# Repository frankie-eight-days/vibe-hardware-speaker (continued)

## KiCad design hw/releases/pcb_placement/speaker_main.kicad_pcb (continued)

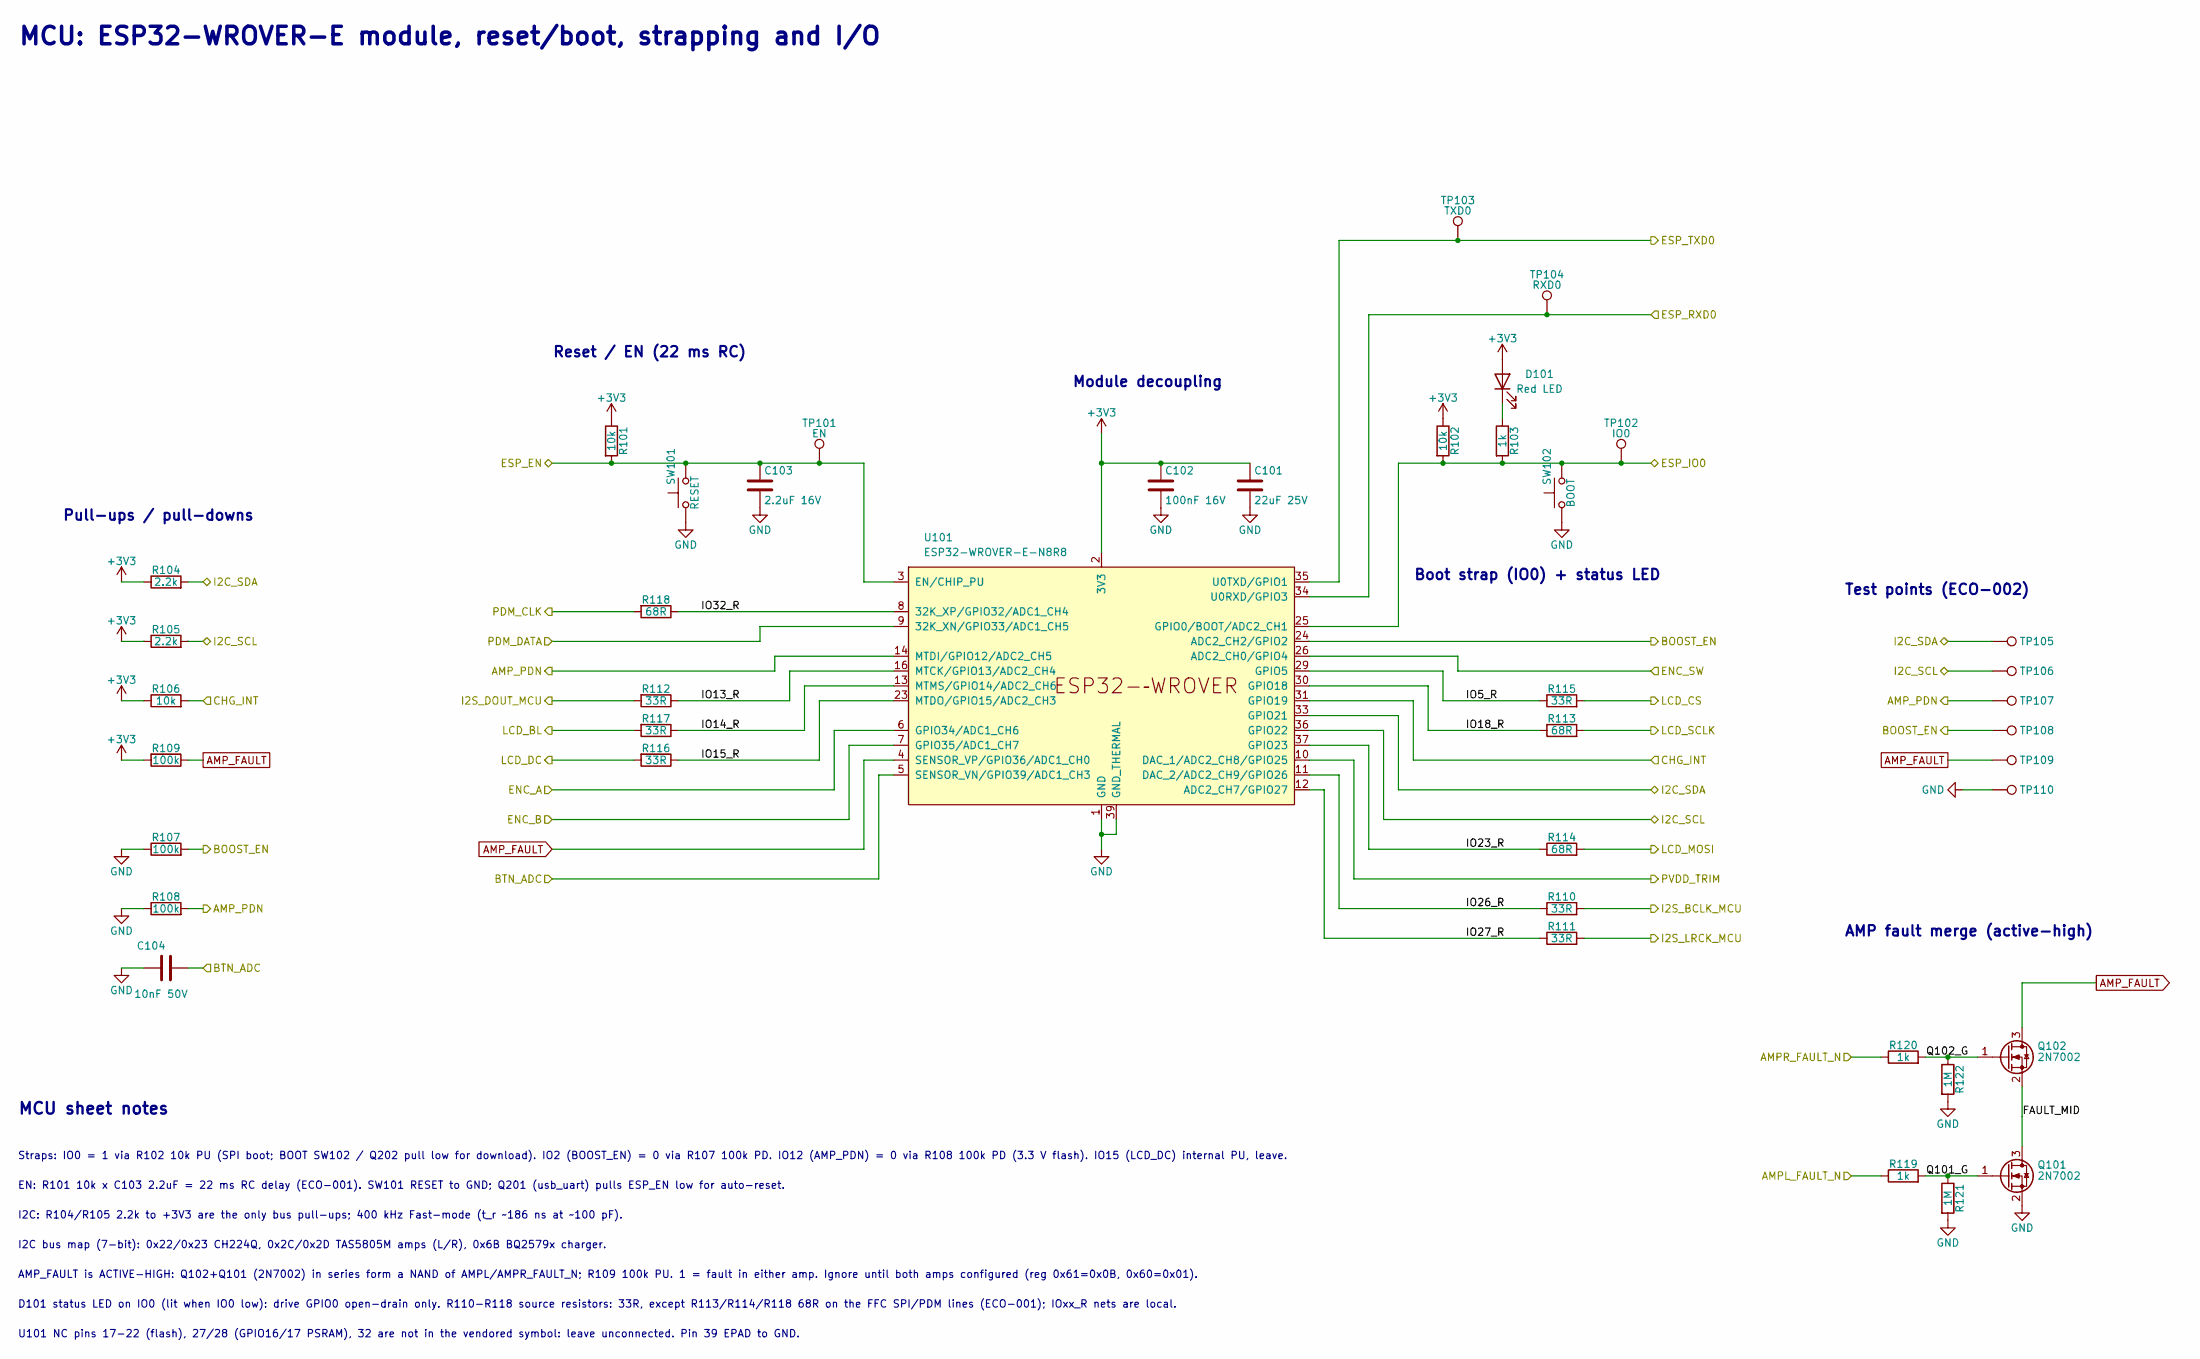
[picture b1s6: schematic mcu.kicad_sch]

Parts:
C101: 22uF 25V; C_0805_2012Metric; LCSC C45783
C102: 100nF 16V; C_0402_1005Metric; LCSC C1525
C103: 2.2uF 16V; C_0402_1005Metric; LCSC C170151
C104: 10nF 50V; C_0402_1005Metric; LCSC C15195
D101: Red LED; LED_0603_1608Metric; LCSC C2286
Q101, Q102: 2N7002; SOT-23; LCSC C8545
R101, R102, R106: 10k; R_0402_1005Metric; LCSC C25744
R103, R119, R120: 1k; R_0402_1005Metric; LCSC C11702
R104, R105: 2.2k; R_0402_1005Metric; LCSC C25879
R107, R108, R109: 100k; R_0402_1005Metric; LCSC C25741
R110, R111, R112, R115, R116, R117: 33R; R_0402_1005Metric; LCSC C25105
R113, R114, R118: 68R; R_0402_1005Metric; LCSC C25131
R121, R122: 1M; R_0402_1005Metric; LCSC C26083
SW101: RESET; SW_Push_1P1T_XKB_TS-1187A; LCSC C318884
SW102: BOOT; SW_Push_1P1T_XKB_TS-1187A; LCSC C318884
TP101: EN; TestPoint_Pad_D1.0mm
TP102: IO0; TestPoint_Pad_D1.0mm
TP103: TXD0; TestPoint_Pad_D1.0mm
TP104: RXD0; TestPoint_Pad_D1.0mm
TP105: I2C_SDA; TestPoint_Pad_D1.0mm
TP106: I2C_SCL; TestPoint_Pad_D1.0mm
TP107: AMP_PDN; TestPoint_Pad_D1.0mm
TP108: BOOST_EN; TestPoint_Pad_D1.0mm
TP109: AMP_FAULT; TestPoint_Pad_D1.0mm
TP110: GND; TestPoint_Pad_D2.0mm
U101: ESP32-WROVER-E-N8R8; ESP32-WROVER-E; LCSC C2973667

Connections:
+3V3: C101.1, C102.1, D101.2 (A), R101.1, R102.1, R104.1, R105.1, R106.1, R109.2, U101.2 (3V3); also elsewhere on the board
/AMPL_FAULT_N: R119.1; also elsewhere on the board
/AMPR_FAULT_N: R120.1; also elsewhere on the board
/AMP_PDN: R108.2, TP107.1 (1_1), U101.14 (MTDI/GPIO12/ADC2_CH5); also elsewhere on the board
/I2C_SCL: R105.2, TP106.1 (1_1), U101.36 (GPIO22); also elsewhere on the board
/I2C_SDA: R104.2, TP105.1 (1_1), U101.33 (GPIO21); also elsewhere on the board
/charger/CHG_INT: R106.2, U101.31 (GPIO19); also elsewhere on the board
/mcu/BOOST_EN: R107.2, TP108.1 (1_1), U101.24 (ADC2_CH2/GPIO2); also elsewhere on the board
/mcu/BTN_ADC: C104.2, U101.5 (SENSOR_VN/GPIO39/ADC1_CH3); also elsewhere on the board
/mcu/ENC_A: U101.6 (GPIO34/ADC1_CH6); also elsewhere on the board
/mcu/ENC_B: U101.7 (GPIO35/ADC1_CH7); also elsewhere on the board
/mcu/ENC_SW: U101.26 (ADC2_CH0/GPIO4); also elsewhere on the board
/mcu/ESP_EN: C103.1, R101.2, SW101.2, TP101.1 (1_1), U101.3 (EN/CHIP_PU); also elsewhere on the board
/mcu/ESP_IO0: R102.2, R103.2, SW102.2, TP102.1 (1_1), U101.25 (GPIO0/BOOT/ADC2_CH1); also elsewhere on the board
/mcu/ESP_RXD0: TP104.1 (1_1), U101.34 (U0RXD/GPIO3); also elsewhere on the board
/mcu/ESP_TXD0: TP103.1 (1_1), U101.35 (U0TXD/GPIO1); also elsewhere on the board
/mcu/FAULT_MID: Q101.3 (D), Q102.2 (S)
/mcu/I2S_BCLK_MCU: R110.2; also elsewhere on the board
/mcu/I2S_DOUT_MCU: R112.2; also elsewhere on the board
/mcu/I2S_LRCK_MCU: R111.2; also elsewhere on the board
/mcu/IO5_R: R115.1, U101.29 (GPIO5)
/mcu/IO13_R: R112.1, U101.16 (MTCK/GPIO13/ADC2_CH4)
/mcu/IO14_R: R117.1, U101.13 (MTMS/GPIO14/ADC2_CH6)
/mcu/IO15_R: R116.1, U101.23 (MTDO/GPIO15/ADC2_CH3)
/mcu/IO18_R: R113.1, U101.30 (GPIO18)
/mcu/IO23_R: R114.1, U101.37 (GPIO23)
/mcu/IO26_R: R110.1, U101.11 (DAC_2/ADC2_CH9/GPIO26)
/mcu/IO27_R: R111.1, U101.12 (ADC2_CH7/GPIO27)
/mcu/IO32_R: R118.1, U101.8 (32K_XP/GPIO32/ADC1_CH4)
/mcu/LCD_BL: R117.2; also elsewhere on the board
/mcu/LCD_CS: R115.2; also elsewhere on the board
/mcu/LCD_DC: R116.2; also elsewhere on the board
/mcu/LCD_MOSI: R114.2; also elsewhere on the board
/mcu/LCD_SCLK: R113.2; also elsewhere on the board
/mcu/PDM_CLK: R118.2; also elsewhere on the board
/mcu/PDM_DATA: U101.9 (32K_XN/GPIO33/ADC1_CH5); also elsewhere on the board
/mcu/PVDD_TRIM: U101.10 (DAC_1/ADC2_CH8/GPIO25); also elsewhere on the board
/mcu/Q101_G: Q101.1 (G), R119.2, R121.1
/mcu/Q102_G: Q102.1 (G), R120.2, R122.1
AMP_FAULT: Q102.3 (D), R109.1, TP109.1 (1_1), U101.4 (SENSOR_VP/GPIO36/ADC1_CH0)
unnamed: D101.1 (K), R103.1

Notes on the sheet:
MCU sheet notes
Straps: IO0 = 1 via R102 10k PU (SPI boot; BOOT SW102 / Q202 pull low for download). IO2 (BOOST_EN) = 0 via R107 100k PD. IO12 (AMP_PDN) = 0 via R108 100k PD (3.3 V flash). IO15 (LCD_DC) internal PU, leave.
I2C: R104/R105 2.2k to +3V3 are the only bus pull-ups; 400 kHz Fast-mode (t_r ~186 ns at ~100 pF).
I2C bus map (7-bit): 0x22/0x23 CH224Q, 0x2C/0x2D TAS5805M amps (L/R), 0x6B BQ2579x charger.
AMP_FAULT is ACTIVE-HIGH: Q102+Q101 (2N7002) in series form a NAND of AMPL/AMPR_FAULT_N; R109 100k PU. 1 = fault in either amp. Ignore until both amps configured (reg 0x61=0x0B, 0x60=0x01).
U101 NC pins 17-22 (flash), 27/28 (GPIO16/17 PSRAM), 32 are not in the vendored symbol: leave unconnected. Pin 39 EPAD to GND.
MCU: ESP32-WROVER-E module, reset/boot, strapping and I/O
Pull-ups / pull-downs
Boot strap (IO0) + status LED
Module decoupling
AMP fault merge (active-high)
EN: R101 10k x C103 2.2uF = 22 ms RC delay (ECO-001). SW101 RESET to GND; Q201 (usb_uart) pulls ESP_EN low for auto-reset.
D101 status LED on IO0 (lit when IO0 low): drive GPIO0 open-drain only. R110-R118 source resistors: 33R, except R113/R114/R118 68R on the FFC SPI/PDM lines (ECO-001); IOxx_R nets are local.
Reset / EN (22 ms RC)
Test points (ECO-002)

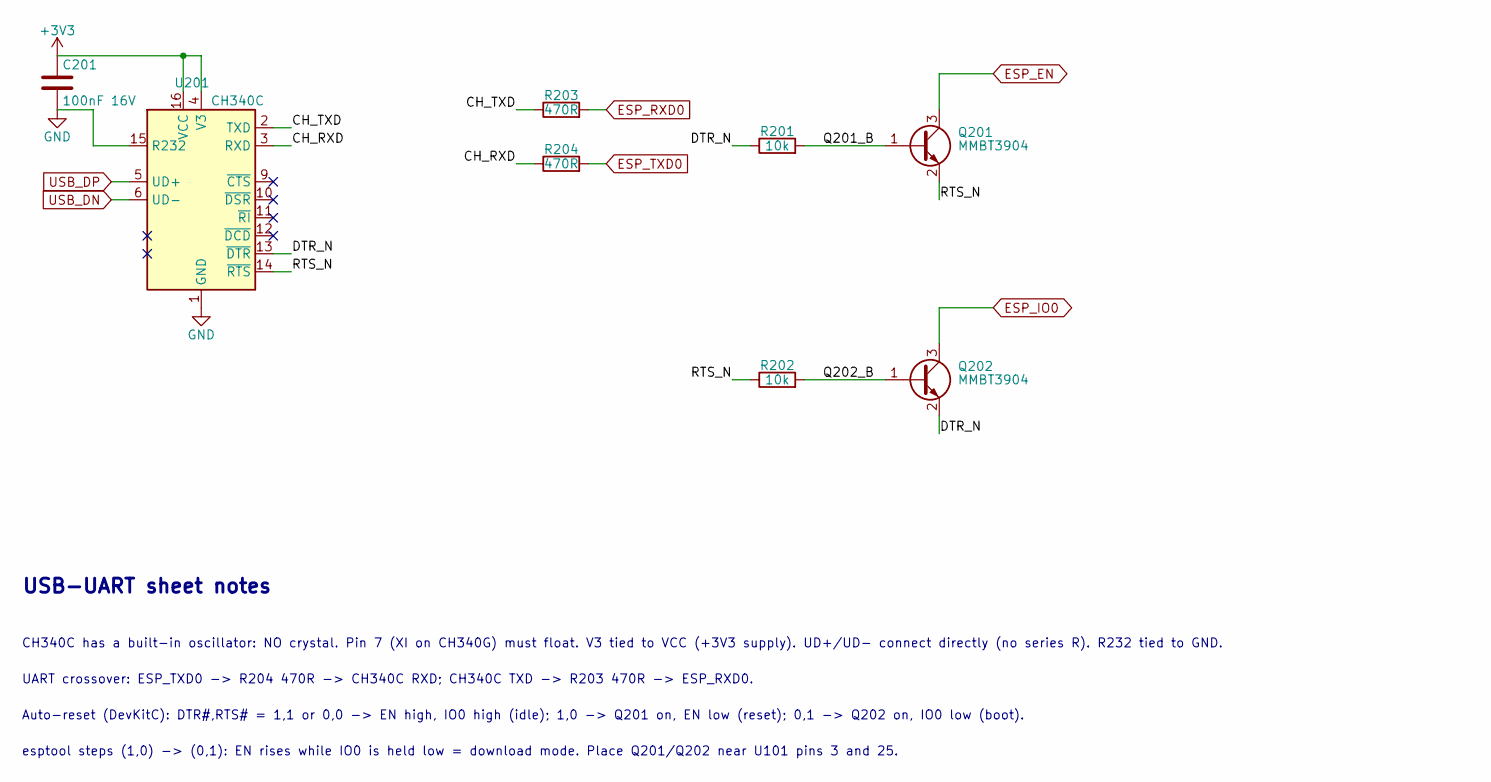
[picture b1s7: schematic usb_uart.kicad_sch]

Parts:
C201: 100nF 16V; C_0402_1005Metric; LCSC C1525
Q201, Q202: MMBT3904; SOT-23; LCSC C20526
R201, R202: 10k; R_0402_1005Metric; LCSC C25744
R203, R204: 470R; R_0402_1005Metric; LCSC C25117
U201: CH340C; SOIC-16_3.9x9.9mm_P1.27mm; LCSC C84681

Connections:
+3V3: C201.1, U201.4 (V3), U201.16 (VCC); also elsewhere on the board
/mcu/ESP_EN: Q201.3 (C); also elsewhere on the board
/mcu/ESP_IO0: Q202.3 (C); also elsewhere on the board
/mcu/ESP_RXD0: R203.2; also elsewhere on the board
/mcu/ESP_TXD0: R204.2; also elsewhere on the board
/usb_power/USB_DN: U201.6 (UD-); also elsewhere on the board
/usb_power/USB_DP: U201.5 (UD+); also elsewhere on the board
/usb_uart/CH_RXD: R204.1, U201.3 (RXD)
/usb_uart/CH_TXD: R203.1, U201.2 (TXD)
/usb_uart/DTR_N: Q202.2 (E), R201.1, U201.13 (~DTR)
/usb_uart/Q201_B: Q201.1 (B), R201.2
/usb_uart/Q202_B: Q202.1 (B), R202.2
/usb_uart/RTS_N: Q201.2 (E), R202.1, U201.14 (~RTS)

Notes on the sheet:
USB-UART sheet notes
CH340C has a built-in oscillator: NO crystal. Pin 7 (XI on CH340G) must float. V3 tied to VCC (+3V3 supply). UD+/UD- connect directly (no series R). R232 tied to GND.
UART crossover: ESP_TXD0 -> R204 470R -> CH340C RXD; CH340C TXD -> R203 470R -> ESP_RXD0.
Auto-reset (DevKitC): DTR#,RTS# = 1,1 or 0,0 -> EN high, IO0 high (idle); 1,0 -> Q201 on, EN low (reset); 0,1 -> Q202 on, IO0 low (boot).
esptool steps (1,0) -> (0,1): EN rises while IO0 is held low = download mode. Place Q201/Q202 near U101 pins 3 and 25.

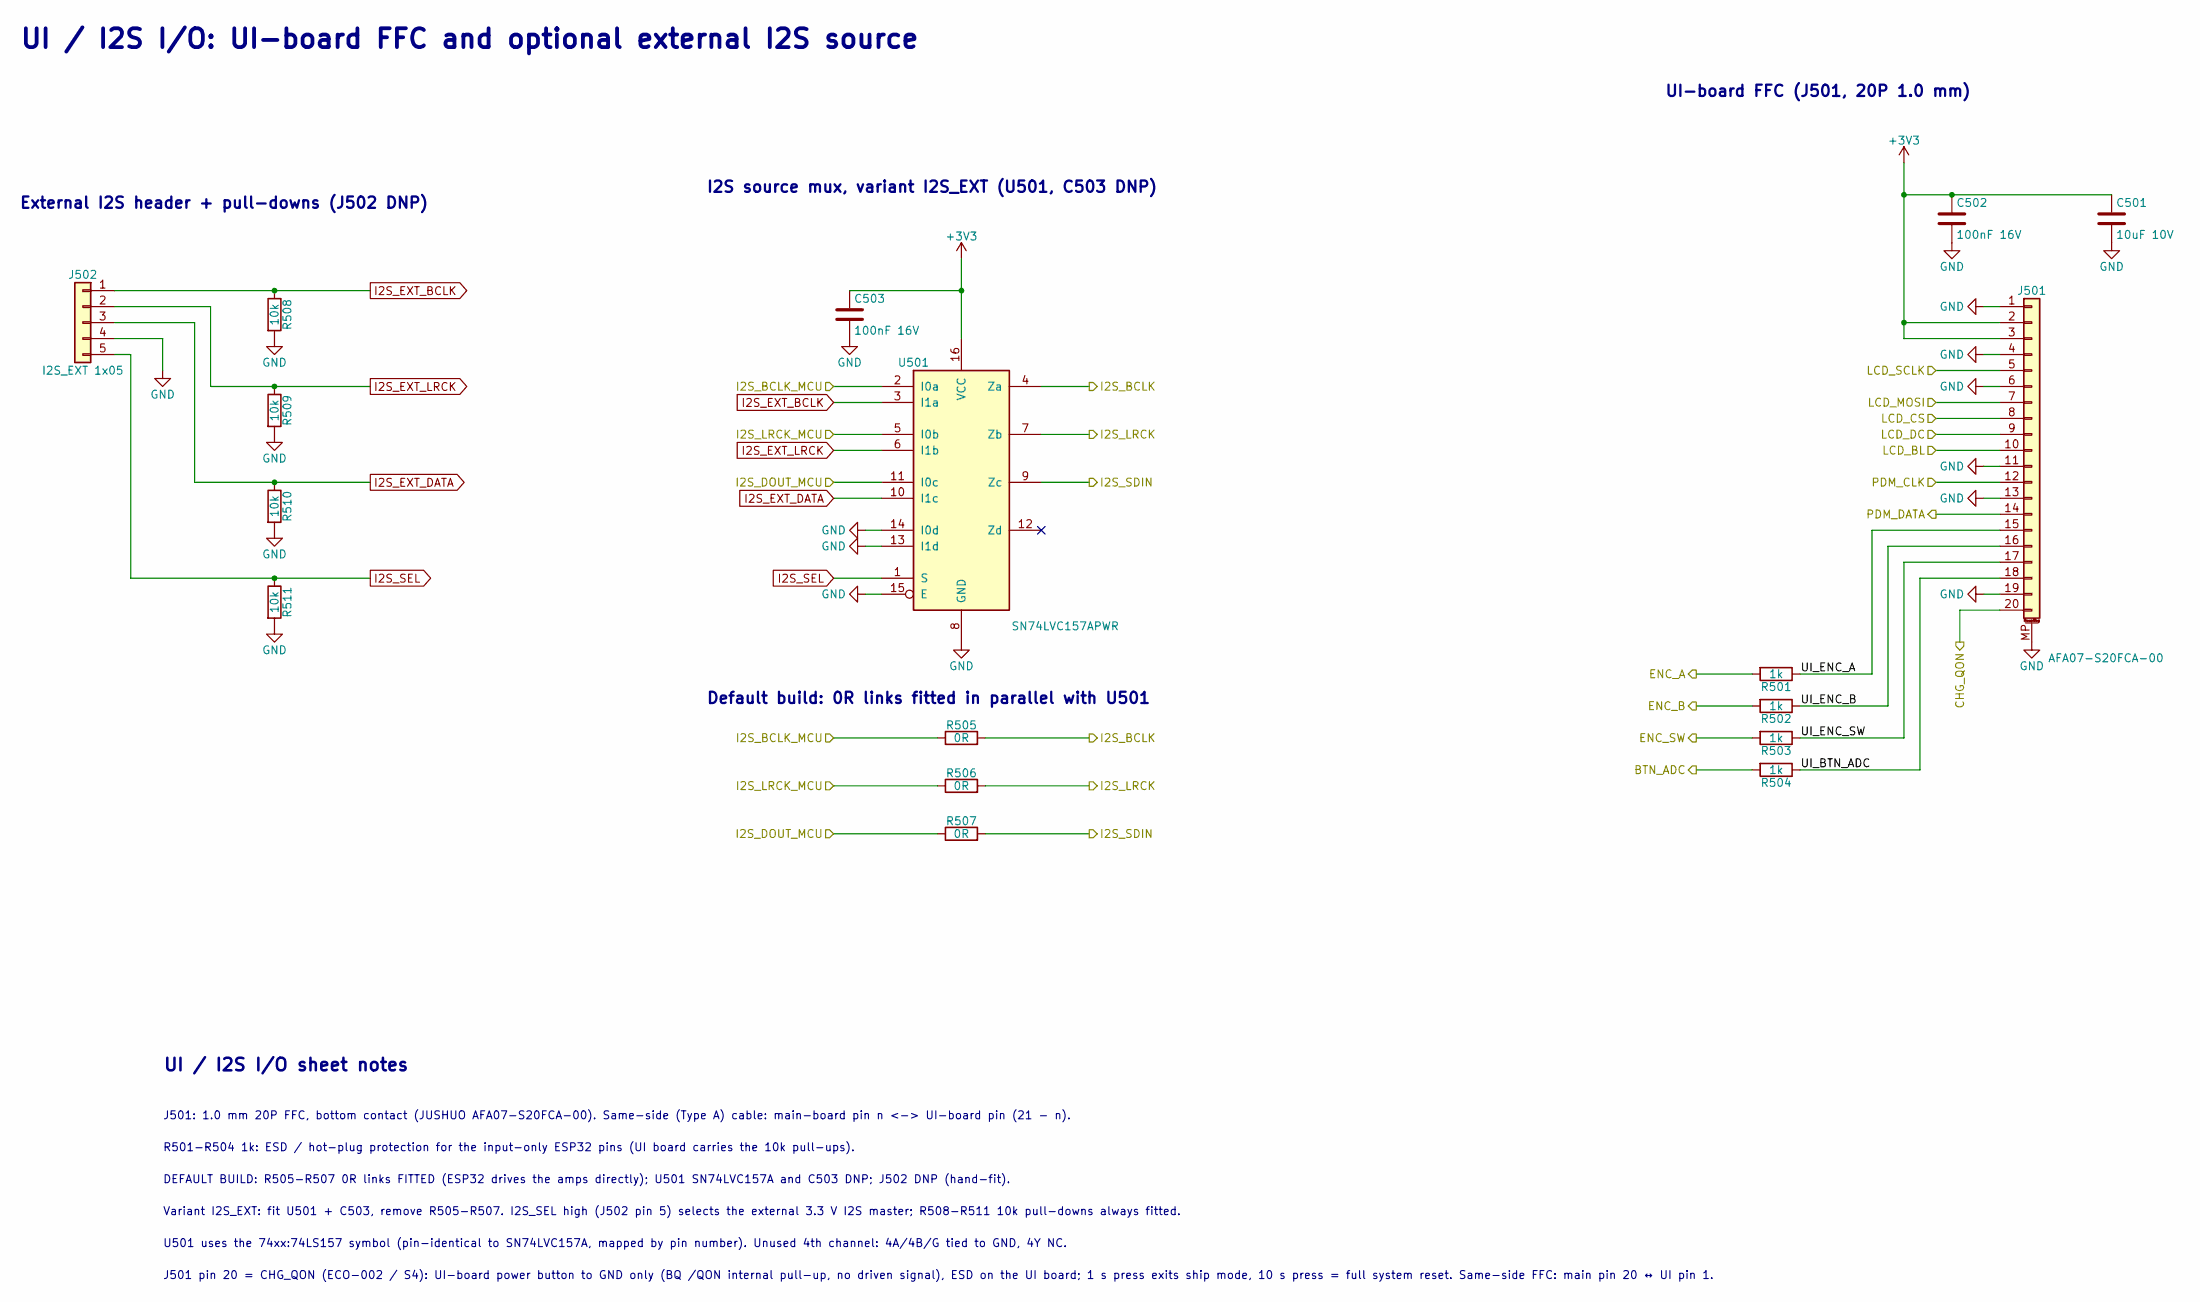
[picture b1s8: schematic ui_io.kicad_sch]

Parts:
C501: 10uF 10V; C_0603_1608Metric; LCSC C19702
C502, C503: 100nF 16V; C_0402_1005Metric; LCSC C1525
J501: AFA07-S20FCA-00; JUSHUO_AFA07-S20FCA-00_1x20-1MP_P1.0mm_Horizontal; LCSC C262724
J502: I2S_EXT 1x05; PinHeader_1x05_P2.54mm_Vertical
R501, R502, R503, R504: 1k; R_0402_1005Metric; LCSC C11702
R505, R506, R507: 0R; R_0402_1005Metric; LCSC C17168
R508, R509, R510, R511: 10k; R_0402_1005Metric; LCSC C25744
U501: SN74LVC157APWR; TSSOP-16_4.4x5mm_P0.65mm; LCSC C406871

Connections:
+3V3: C501.1, C502.1, C503.1, J501.2, J501.3, U501.16 (VCC); also elsewhere on the board
/CHG_QON: J501.20; also elsewhere on the board
/I2S_BCLK: R505.2, U501.4 (Za); also elsewhere on the board
/I2S_LRCK: R506.2, U501.7 (Zb); also elsewhere on the board
/I2S_SDIN: R507.2, U501.9 (Zc); also elsewhere on the board
/mcu/BTN_ADC: R504.2; also elsewhere on the board
/mcu/ENC_A: R501.2; also elsewhere on the board
/mcu/ENC_B: R502.2; also elsewhere on the board
/mcu/ENC_SW: R503.2; also elsewhere on the board
/mcu/I2S_BCLK_MCU: R505.1, U501.2 (I0a); also elsewhere on the board
/mcu/I2S_DOUT_MCU: R507.1, U501.11 (I0c); also elsewhere on the board
/mcu/I2S_LRCK_MCU: R506.1, U501.5 (I0b); also elsewhere on the board
/mcu/LCD_BL: J501.10; also elsewhere on the board
/mcu/LCD_CS: J501.8; also elsewhere on the board
/mcu/LCD_DC: J501.9; also elsewhere on the board
/mcu/LCD_MOSI: J501.7; also elsewhere on the board
/mcu/LCD_SCLK: J501.5; also elsewhere on the board
/mcu/PDM_CLK: J501.12; also elsewhere on the board
/mcu/PDM_DATA: J501.14; also elsewhere on the board
/ui_io/UI_BTN_ADC: J501.18, R504.1
/ui_io/UI_ENC_A: J501.15, R501.1
/ui_io/UI_ENC_B: J501.16, R502.1
/ui_io/UI_ENC_SW: J501.17, R503.1
I2S_EXT_BCLK: J502.1, R508.1, U501.3 (I1a)
I2S_EXT_DATA: J502.3, R510.1, U501.10 (I1c)
I2S_EXT_LRCK: J502.2, R509.1, U501.6 (I1b)
I2S_SEL: J502.5, R511.1, U501.1 (S)

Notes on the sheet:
UI / I2S I/O sheet notes
J501: 1.0 mm 20P FFC, bottom contact (JUSHUO AFA07-S20FCA-00). Same-side (Type A) cable: main-board pin n <-> UI-board pin (21 - n).
R501-R504 1k: ESD / hot-plug protection for the input-only ESP32 pins (UI board carries the 10k pull-ups).
DEFAULT BUILD: R505-R507 0R links FITTED (ESP32 drives the amps directly); U501 SN74LVC157A and C503 DNP; J502 DNP (hand-fit).
Variant I2S_EXT: fit U501 + C503, remove R505-R507. I2S_SEL high (J502 pin 5) selects the external 3.3 V I2S master; R508-R511 10k pull-downs always fitted.
U501 uses the 74xx:74LS157 symbol (pin-identical to SN74LVC157A, mapped by pin number). Unused 4th channel: 4A/4B/G tied to GND, 4Y NC.
UI / I2S I/O: UI-board FFC and optional external I2S source
External I2S header + pull-downs (J502 DNP)
I2S source mux, variant I2S_EXT (U501, C503 DNP)
Default build: 0R links fitted in parallel with U501
UI-board FFC (J501, 20P 1.0 mm)
J501 pin 20 = CHG_QON (ECO-002 / S4): UI-board power button to GND only (BQ /QON internal pull-up, no driven signal), ESD on the UI board; 1 s press exits ship mode, 10 s press = full system reset. Same-side FFC: main pin 20 ↔ UI pin 1.

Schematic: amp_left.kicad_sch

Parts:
C301: 470uF 35V; CP_Elec_10x10; LCSC C2836436
C302, C303, C305, C306: 10uF 50V; C_1206_3216Metric; LCSC C13585
C304, C307: 100nF 50V; C_0402_1005Metric; LCSC C307331
C308: 4.7uF 16V; C_0603_1608Metric; LCSC C19666
C309: 100nF 16V; C_0402_1005Metric; LCSC C1525
C310, C311: 1uF 50V; C_0603_1608Metric; LCSC C15849
C312, C313, C314, C315: 220nF 25V; C_0603_1608Metric; LCSC C21120
C316, C317, C318, C319: 1uF 50V; C_0805_2012Metric; LCSC C28323
J301: Woofer L (8R); JST_VH_B2P-VH_1x02_P3.96mm_Vertical; LCSC C160315
J302: Tweeter L (4R); JST_VH_B2P-VH_1x02_P3.96mm_Vertical; LCSC C160315
L301, L302, L303, L304: 10uH; L_Changjiang_FXL0630; LCSC C167223
R301: 4.7k; R_0402_1005Metric; LCSC C25900
U301: TAS5805MPWPR; TSSOP-28-1EP_4.4x9.7mm_P0.65mm_EP3.4x9.7mm_Mask3.1x4.05mm_T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; LCSC C478472

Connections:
+3V3: C308.1, C309.1, R301.1, U301.2 (DVDD); also elsewhere on the board
/AMPL_FAULT_N: R301.2, U301.3 (ADR/~FAULT); also elsewhere on the board
/AMP_PDN: U301.12 (~PDN); also elsewhere on the board
/I2C_SCL: U301.11 (SCL); also elsewhere on the board
/I2C_SDA: U301.10 (SDA); also elsewhere on the board
/I2S_BCLK: U301.7 (SCLK); also elsewhere on the board
/I2S_LRCK: U301.6 (LRCLK); also elsewhere on the board
/I2S_SDIN: U301.8 (SDIN); also elsewhere on the board
/amp_left/AL_AVDD: C310.1, U301.13 (AVDD)
/amp_left/AL_BSTA_N: C313.1, U301.22 (BST_A-)
/amp_left/AL_BSTA_P: C312.1, U301.25 (BST_A+)
/amp_left/AL_BSTB_N: C315.1, U301.21 (BST_B-)
/amp_left/AL_BSTB_P: C314.1, U301.18 (BST_B+)
/amp_left/AL_OUTA_N: C313.2, L302.1, U301.23 (OUT_A-)
/amp_left/AL_OUTA_P: C312.2, L301.1, U301.26 (OUT_A+)
/amp_left/AL_OUTB_N: C315.2, L304.1, U301.20 (OUT_B-)
/amp_left/AL_OUTB_P: C314.2, L303.1, U301.17 (OUT_B+)
/amp_left/AL_VRDIG: C311.1, U301.4 (VR_DIG)
/amp_left/PVDD: C301.1, C302.1, C303.1, C304.1, C305.1, C306.1, C307.1, U301.15 (PVDD), U301.16 (PVDD), U301.27 (PVDD), U301.28 (PVDD); also elsewhere on the board
/amp_left/SPK_TL_N: C319.1, J302.2, L304.2
/amp_left/SPK_TL_P: C318.1, J302.1, L303.2
/amp_left/SPK_WL_N: C317.1, J301.2, L302.2
/amp_left/SPK_WL_P: C316.1, J301.1, L301.2

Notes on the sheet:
AMP LEFT - TAS5805M (U301), BTL, ch A = woofer, ch B = tweeter
I2C address 0x2C (7-bit): R301 = 4.7k ADR/FAULT strap to DVDD (+3V3). amp_right: R401 = 15k -> 0x2D. Pin 3 is also FAULTZ -> AMPL_FAULT_N (merged on mcu sheet).
PVDD = 18.0 V (boost, power sheet); DVDD = +3V3. AVDD (5 V) and VR_DIG (1.5 V) are internal regulator outputs: cap only, no other load.
Output LC per leg: 10 uH (FXL0630-100-M, Isat 5.5 A) + 1 uF 50 V X7R to GND -> BTL f0 ~ 50 kHz. Fsw = 768 kHz (FSW_SEL = 000), Hybrid modulation.
Speaker terminals are BTL and float at ~PVDD/2: never tie either terminal to GND. SDOUT (pin 9) not used.
Ch A = woofer J301, 8 ohm (ND65-8): DRC/AGL at max 15.5 V pk. Ch B = tweeter J302, 4 ohm (OT19NC00-04): limiter max 8 V pk after crossover is MANDATORY (OCP 5 A).
Layout: C304 + C302/C303 at pins 15/16, C307 + C305/C306 at pins 27/28 (100 nF within 1 mm), C301 between groups. Bootstrap C312-C315 straight BST to OUT, top layer, no vias.

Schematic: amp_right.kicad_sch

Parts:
C401: 470uF 35V; CP_Elec_10x10; LCSC C2836436
C402, C403, C405, C406: 10uF 50V; C_1206_3216Metric; LCSC C13585
C404, C407: 100nF 50V; C_0402_1005Metric; LCSC C307331
C408: 4.7uF 16V; C_0603_1608Metric; LCSC C19666
C409: 100nF 16V; C_0402_1005Metric; LCSC C1525
C410, C411: 1uF 50V; C_0603_1608Metric; LCSC C15849
C412, C413, C414, C415: 220nF 25V; C_0603_1608Metric; LCSC C21120
C416, C417, C418, C419: 1uF 50V; C_0805_2012Metric; LCSC C28323
J401: Woofer R (8R); JST_VH_B2P-VH_1x02_P3.96mm_Vertical; LCSC C160315
J402: Tweeter R (4R); JST_VH_B2P-VH_1x02_P3.96mm_Vertical; LCSC C160315
L401, L402, L403, L404: 10uH; L_Changjiang_FXL0630; LCSC C167223
R401: 15k; R_0402_1005Metric; LCSC C25756
TP401: PVDD; TestPoint_Pad_D2.0mm
U401: TAS5805MPWPR; TSSOP-28-1EP_4.4x9.7mm_P0.65mm_EP3.4x9.7mm_Mask3.1x4.05mm_T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; LCSC C478472

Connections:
+3V3: C408.1, C409.1, R401.1, U401.2 (DVDD); also elsewhere on the board
/AMPR_FAULT_N: R401.2, U401.3 (ADR/~FAULT); also elsewhere on the board
/AMP_PDN: U401.12 (~PDN); also elsewhere on the board
/I2C_SCL: U401.11 (SCL); also elsewhere on the board
/I2C_SDA: U401.10 (SDA); also elsewhere on the board
/I2S_BCLK: U401.7 (SCLK); also elsewhere on the board
/I2S_LRCK: U401.6 (LRCLK); also elsewhere on the board
/I2S_SDIN: U401.8 (SDIN); also elsewhere on the board
/amp_left/PVDD: C401.1, C402.1, C403.1, C404.1, C405.1, C406.1, C407.1, TP401.1 (1_1), U401.15 (PVDD), U401.16 (PVDD), U401.27 (PVDD), U401.28 (PVDD); also elsewhere on the board
/amp_right/AR_AVDD: C410.1, U401.13 (AVDD)
/amp_right/AR_BSTA_N: C413.1, U401.22 (BST_A-)
/amp_right/AR_BSTA_P: C412.1, U401.25 (BST_A+)
/amp_right/AR_BSTB_N: C415.1, U401.21 (BST_B-)
/amp_right/AR_BSTB_P: C414.1, U401.18 (BST_B+)
/amp_right/AR_OUTA_N: C413.2, L402.1, U401.23 (OUT_A-)
/amp_right/AR_OUTA_P: C412.2, L401.1, U401.26 (OUT_A+)
/amp_right/AR_OUTB_N: C415.2, L404.1, U401.20 (OUT_B-)
/amp_right/AR_OUTB_P: C414.2, L403.1, U401.17 (OUT_B+)
/amp_right/AR_VRDIG: C411.1, U401.4 (VR_DIG)
/amp_right/SPK_TR_N: C419.1, J402.2, L404.2
/amp_right/SPK_TR_P: C418.1, J402.1, L403.2
/amp_right/SPK_WR_N: C417.1, J401.2, L402.2
/amp_right/SPK_WR_P: C416.1, J401.1, L401.2

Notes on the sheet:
AMP RIGHT - TAS5805M (U401), BTL, ch A = woofer, ch B = tweeter
Design notes
I2C address 0x2D (7-bit): R401 = 15k ADR/FAULT strap to DVDD (+3V3). amp_left: R301 = 4.7k -> 0x2C. Pin 3 is also FAULTZ -> AMPR_FAULT_N (merged on mcu sheet).
PVDD = 18.0 V (boost, power sheet); DVDD = +3V3. AVDD (5 V) and VR_DIG (1.5 V) are internal regulator outputs: cap only, no other load.
Output LC per leg: 10 uH (FXL0630-100-M, Isat 5.5 A) + 1 uF 50 V X7R to GND -> BTL f0 ~ 50 kHz. Fsw = 768 kHz (FSW_SEL = 000), Hybrid modulation.
Ch A = woofer J401, 8 ohm (ND65-8): DRC/AGL at max 15.5 V pk. Ch B = tweeter J402, 4 ohm (OT19NC00-04): limiter max 8 V pk after crossover is MANDATORY (OCP 5 A).
Layout: C404 + C402/C403 at pins 15/16, C407 + C405/C406 at pins 27/28 (100 nF within 1 mm), C401 between groups. Bootstrap C412-C415 straight BST to OUT, top layer, no vias.
Speaker terminals are BTL and float at ~PVDD/2: never tie either terminal to GND. SDOUT (pin 9) not used.
PVDD decoupling (100 nF closest to pins 15/16 and 27/28)
Bootstrap caps (BST to OUT)
Output LC filters (BTL)
Speaker outputs

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
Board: 4 copper layers, 281 parts (29 on the bottom side), 155 nets, no tracks yet.

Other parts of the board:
BRD1: BoardOutline_speaker_main
C721: 100nF 50V; C_0603_1608Metric
FID1, FID2, FID3: Fiducial_1mm_Mask2mm
H1, H2, H3, H4, H5, H6: MountingHole_3.2mm_M3
TP301: I2S_BCLK; TestPoint_Pad_D1.0mm
TP302: I2S_LRCK; TestPoint_Pad_D1.0mm
TP303: I2S_SDIN; TestPoint_Pad_D1.0mm
TP304: PVDD; TestPoint_Pad_D2.0mm
TP305: GND; TestPoint_Pad_D2.0mm
TP703: SFET_G; TestPoint_Pad_D1.0mm

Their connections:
/I2S_BCLK: TP301.1 (1_1); also elsewhere on the board
/I2S_LRCK: TP302.1 (1_1); also elsewhere on the board
/I2S_SDIN: TP303.1 (1_1); also elsewhere on the board
/amp_left/PVDD: TP304.1 (1_1); also elsewhere on the board
/charger/CHG_BAT: C721.2; also elsewhere on the board
/charger/SFET_G: C721.1, TP703.1 (1_1); also elsewhere on the board

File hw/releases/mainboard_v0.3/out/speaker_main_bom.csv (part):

"Designator","Value","Footprint","LCSC","DNP","Qty"
"C101","22uF 25V","Capacitor_SMD:C_0805_2012Metric","C45783","","1"
"C102,C201,C309,C409,C502","100nF 16V","Capacitor_SMD:C_0402_1005Metric","C1525","","5"
"C103","2.2uF 16V","Capacitor_SMD:C_0402_1005Metric","C170151","","1"
"C104","10nF 50V","Capacitor_SMD:C_0402_1005Metric","C15195","","1"
"C301,C401,C920","470uF 35V","Capacitor_SMD:CP_Elec_10x10","C2836436","","3"
"C302,C303,C305,C306,C402,C403,C405,C406,C701,C702,C704,C705,C706,C906,C907,C908,C909,C910,C911,C912,C913","10uF 50V","Capacitor_SMD:C_1206_3216Metric","C13585","","21"
"C304,C307,C404,C407","100nF 50V","Capacitor_SMD:C_0402_1005Metric","C307331","","4"
"C308,C408,C710,C904","4.7uF 16V","Capacitor_SMD:C_0603_1608Metric","C19666","","4"
"C310,C311,C410,C411,C604,C917,C918","1uF 50V","Capacitor_SMD:C_0603_1608Metric","C15849","","7"
"C312,C313,C314,C315,C412,C413,C414,C415","220nF 25V","Capacitor_SMD:C_0603_1608Metric","C21120","","8"
"C316,C317,C318,C319,C416,C417,C418,C419","1uF 50V","Capacitor_SMD:C_0805_2012Metric","C28323","","8"
"C501","10uF 10V","Capacitor_SMD:C_0603_1608Metric","C19702","","1"
"C503","100nF 16V","Capacitor_SMD:C_0402_1005Metric","C1525","DNP","1"
"C601,C603,C703,C707,C716,C801,C802,C804,C805,C903,C905,C914,C953,C955,C959","100nF 50V","Capacitor_SMD:C_0603_1608Metric","C14663","","15"
"C602","2.2uF 50V","Capacitor_SMD:C_0805_2012Metric","C377773","DNP","1"
"C605","47uF 35V","Capacitor_SMD:CP_Elec_6.3x5.7","C134832","","1"
"C708,C709","47nF 50V","Capacitor_SMD:C_0603_1608Metric","C1622","","2"
"C711,C712,C713,C714,C715,C717,C718,C951,C952","10uF 25V","Capacitor_SMD:C_0805_2012Metric","C15850","","9"
"C719","47nF 50V","Capacitor_SMD:C_0603_1608Metric","C1622","DNP","1"
"C720","10nF 50V","Capacitor_SMD:C_0603_1608Metric","C57112","DNP","1"
"C721","100nF 50V","Capacitor_SMD:C_0603_1608Metric","C14663","DNP","1"
"C803","10nF 50V","Capacitor_SMD:C_0603_1608Metric","C57112","","1"
"C901,C902,C957,C958","22uF 25V","Capacitor_SMD:C_1206_3216Metric","C12891","","4"
"C915","15nF 50V","Capacitor_SMD:C_0603_1608Metric","C1596","","1"
"C916","10pF 50V","Capacitor_SMD:C_0603_1608Metric","C1634","","1"
"C954","33nF 50V","Capacitor_SMD:C_0603_1608Metric","C21117","","1"
"C956","10pF 50V","Capacitor_SMD:C_0603_1608Metric","C1634","DNP","1"
"D101","Red LED","LED_SMD:LED_0603_1608Metric","C2286","","1"
"D601","SMF24A","Diode_SMD:D_SOD-123F","C123810","","1"
"D701","Green KT-0805G","LED_SMD:LED_0805_2012Metric","C2297","","1"
"D901","1N4148W","Diode_SMD:D_SOD-123","C81598","","1"
"D951","Red KT-0603R","LED_SMD:LED_0603_1608Metric","C2286","DNP","1"
"F801","0451010.MRL 10A","speaker:Fuse_2410_6125Metric","C44479","","1"
"J301","Woofer L (8R)","Connector_JST:JST_VH_B2P-VH_1x02_P3.96mm_Vertical","C160315","","1"
"J302","Tweeter L (4R)","Connector_JST:JST_VH_B2P-VH_1x02_P3.96mm_Vertical","C160315","","1"
"J401","Woofer R (8R)","Connector_JST:JST_VH_B2P-VH_1x02_P3.96mm_Vertical","C160315","","1"
"J402","Tweeter R (4R)","Connector_JST:JST_VH_B2P-VH_1x02_P3.96mm_Vertical","C160315","","1"
"J501","AFA07-S20FCA-00","Connector_FFC-FPC:JUSHUO_AFA07-S20FCA-00_1x20-1MP_P1.0mm_Horizontal","C262724","","1"
"J502","I2S_EXT 1x05","Connector_PinHeader_2.54mm:PinHeader_1x05_P2.54mm_Vertical","","DNP","1"
"J601","USB-C 16P TYPE-C-31-M-12","Connector_USB:USB_C_Receptacle_HRO_TYPE-C-31-M-12","C165948","","1"
"J801","XT30PW-M","Connector_AMASS:AMASS_XT30PW-M_1x02_P2.50mm_Horizontal","C431092","","1"
"J802","B3B-XH-A","Connector_JST:JST_XH_B3B-XH-A_1x03_P2.50mm_Vertical","C144394","","1"
"J803","B2B-PH-K-S","Connector_JST:JST_PH_B2B-PH-K_1x02_P2.00mm_Vertical","C131337","","1"
"JP801,JP802","open","Jumper:SolderJumper-2_P1.3mm_Open_RoundedPad1.0x1.5mm","","","2"
"JP803","bridged 1-2 = J803 pack NTC","Jumper:SolderJumper-3_P1.3mm_Bridged12_RoundedPad1.0x1.5mm","","","1"
"L301,L302,L303,L304,L401,L402,L403,L404","10uH","Inductor_SMD:L_Changjiang_FXL0630","C167223","","8"
"L701","2.2uH FXL0630-2R2-M","Inductor_SMD:L_Changjiang_FXL0630","C167218","","1"
"L901","2.2uH FXL1040","Inductor_SMD:L_Changjiang_FXL1040","C167228","","1"
"L951","4.7uH FXL0420","Inductor_SMD:L_Changjiang_FXL0420","C167208","","1"
"Q101,Q102","2N7002","Package_TO_SOT_SMD:SOT-23","C8545","","2"
"Q201,Q202","MMBT3904","Package_TO_SOT_SMD:SOT-23","C20526","","2"
"Q601,Q602,Q803,Q804","AO3400A","Package_TO_SOT_SMD:SOT-23","C20917","","4"
"Q701,Q801,Q802","NCEP3065QU","Package_SON:VSON-8_3.3x3.3mm_P0.65mm_NexFET","C502964","","3"
"R101,R102,R106,R201,R202,R508,R509,R510,R511","10k","Resistor_SMD:R_0402_1005Metric","C25744","","9"
"R103,R119,R120,R501,R502,R503,R504","1k","Resistor_SMD:R_0402_1005Metric","C11702","","7"
"R104,R105","2.2k","Resistor_SMD:R_0402_1005Metric","C25879","","2"
"R107,R108,R109","100k","Resistor_SMD:R_0402_1005Metric","C25741","","3"
"R110,R111,R112,R115,R116,R117","33R","Resistor_SMD:R_0402_1005Metric","C25105","","6"
"R113,R114,R118","68R","Resistor_SMD:R_0402_1005Metric","C25131","","3"
"R121,R122","1M","Resistor_SMD:R_0402_1005Metric","C26083","","2"
"R203,R204","470R","Resistor_SMD:R_0402_1005Metric","C25117","","2"
"R301","4.7k","Resistor_SMD:R_0402_1005Metric","C25900","","1"
"R401","15k","Resistor_SMD:R_0402_1005Metric","C25756","","1"
"R505,R506,R507","0R","Resistor_SMD:R_0402_1005Metric","C17168","","3"
"R601","2.0R","Resistor_SMD:R_0805_2012Metric","C2930265","DNP","1"
"R602","56k 1%","Resistor_SMD:R_0603_1608Metric","C23206","","1"
"R603,R604","100k","Resistor_SMD:R_0603_1608Metric","C25803","","2"
"R701","8.2k 1%","Resistor_SMD:R_0603_1608Metric","C25981","","1"
"R702","51k 1%","Resistor_SMD:R_0603_1608Metric","C23196","","1"
"R703,R903","100k 1%","Resistor_SMD:R_0603_1608Metric","C25803","","2"
"R704","5.1k 1%","Resistor_SMD:R_0603_1608Metric","C23186","","1"
"R705","30k 1%","Resistor_SMD:R_0603_1608Metric","C22984","","1"
"R706,R804,R807","100R","Resistor_SMD:R_0603_1608Metric","C22775","","3"
"R707,R908,R909","10k","Resistor_SMD:R_0603_1608Metric","C25804","","3"
"R708,R803","1k","Resistor_SMD:R_0603_1608Metric","C21190","","2"
"R709,R953","0R","Resistor_SMD:R_0603_1608Metric","C21189","","2"
"R710","100k","Resistor_SMD:R_0603_1608Metric","C25803","DNP","1"
"R801,R802","330R","Resistor_SMD:R_0603_1608Metric","C23138","","2"
"R805,R806,R808,R809","120R 1%","Resistor_SMD:R_1206_3216Metric","C17909","","4"
"R810,R811","1M","Resistor_SMD:R_0603_1608Metric","C22935","","2"
"R901,R904,R951","300k 1%","Resistor_SMD:R_0603_1608Metric","C23024","","3"
"R902,R952","82k 1%","Resistor_SMD:R_0603_1608Metric","C23254","","2"
"R905,R955","24k 1%","Resistor_SMD:R_0603_1608Metric","C23352","","2"
"R906","200k 1%","Resistor_SMD:R_0603_1608Metric","C25811","","1"
"R907","68k 1%","Resistor_SMD:R_0603_1608Metric","C23231","","1"
"R954","75k 1%","Resistor_SMD:R_0603_1608Metric","C23242","","1"
"R956","1k","Resistor_SMD:R_0603_1608Metric","C21190","DNP","1"
"SW101","RESET","Button_Switch_SMD:SW_Push_1P1T_XKB_TS-1187A","C318884","","1"
"SW102","BOOT","Button_Switch_SMD:SW_Push_1P1T_XKB_TS-1187A","C318884","","1"
"SW701","TS-1187A-B-A-B","Button_Switch_SMD:SW_Push_1P1T_XKB_TS-1187A","C318884","","1"
"TH801","10k B3435","Resistor_SMD:R_0603_1608Metric","C2889048","","1"
"TP101","EN","TestPoint:TestPoint_Pad_D1.0mm","","","1"
"TP102","IO0","TestPoint:TestPoint_Pad_D1.0mm","","","1"
"TP103","TXD0","TestPoint:TestPoint_Pad_D1.0mm","","","1"
"TP104","RXD0","TestPoint:TestPoint_Pad_D1.0mm","","","1"
"TP105","I2C_SDA","TestPoint:TestPoint_Pad_D1.0mm","","","1"
"TP106","I2C_SCL","TestPoint:TestPoint_Pad_D1.0mm","","","1"
"TP107","AMP_PDN","TestPoint:TestPoint_Pad_D1.0mm","","","1"
"TP108","BOOST_EN","TestPoint:TestPoint_Pad_D1.0mm","","","1"
"TP109","AMP_FAULT","TestPoint:TestPoint_Pad_D1.0mm","","","1"
"TP110,TP305,TP952,TP953,TP954","GND","TestPoint:TestPoint_Pad_D2.0mm","","","5"
"TP301","I2S_BCLK","TestPoint:TestPoint_Pad_D1.0mm","","","1"
"TP302","I2S_LRCK","TestPoint:TestPoint_Pad_D1.0mm","","","1"
"TP303","I2S_SDIN","TestPoint:TestPoint_Pad_D1.0mm","","","1"
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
